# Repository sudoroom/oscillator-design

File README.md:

#sudosynth
##making music from garbage electronics

KiCad Design for an Oscillator Board
originally by rayendumeldust
contributions by jerkey

license:  GPL V3

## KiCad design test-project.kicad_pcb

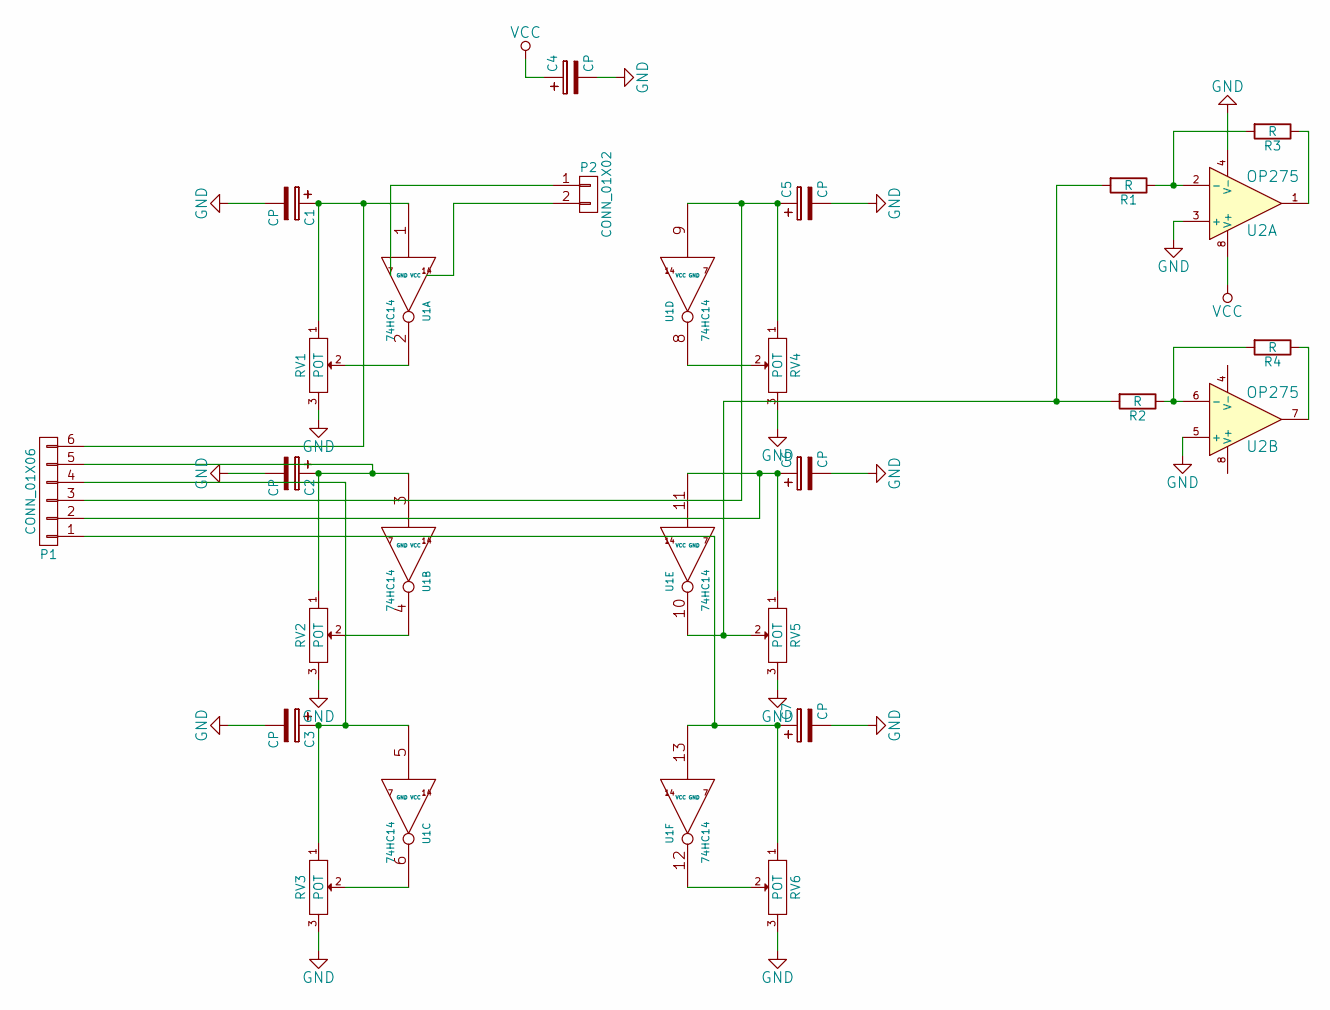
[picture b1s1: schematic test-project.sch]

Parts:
C1, C2, C3, C4, C5: CP; C_Radial_D8_L13_P3.8
C6, C7: CP; C_Radial_D8_L21_P3.8
P1: CONN_01X06; bornier6
P2: CONN_01X02; AK300-2
R1, R2, R3, R4: R; Resistor_Horizontal_RM10mm
RV1, RV2, RV3, RV4, RV5, RV6: POT; Potentiometer_Trimmer-Piher_PT15-B_vertical
U1: 74HC14; DIP-14__300_ELL
U2: OP275; DIP-8__300_ELL

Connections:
GND: C1.2, C2.2, C3.2, C4.2, C5.2, C6.2, C7.2, RV1.3, RV2.3, RV3.3, RV4.3, RV5.3, RV6.3, U2.3 (+), U2.4 (V-), U2.5 (+)
unnamed: C1.1, P1.6, RV1.1, U1.1
unnamed: C2.1, P1.5, RV2.1, U1.3
unnamed: C3.1, P1.4, RV3.1, U1.5
unnamed: C5.1, P1.3, RV4.1, U1.9
unnamed: C6.1, P1.2, RV5.1, U1.11
unnamed: C7.1, P1.1, RV6.1, U1.13
unnamed: P2.1, U1.7 (GND)
unnamed: P2.2, U1.14 (VCC)
unnamed: R1.1, R3.2, U2.2 (-)
unnamed: R1.2, R2.2, RV5.2, U1.10
unnamed: R2.1, R4.2, U2.6 (-)
unnamed: R3.1, U2.1
unnamed: R4.1, U2.7
unnamed: RV1.2, U1.2
unnamed: RV2.2, U1.4
unnamed: RV3.2, U1.6
unnamed: RV4.2, U1.8
unnamed: RV6.2, U1.12
VCC: C4.1, U2.8 (V+)

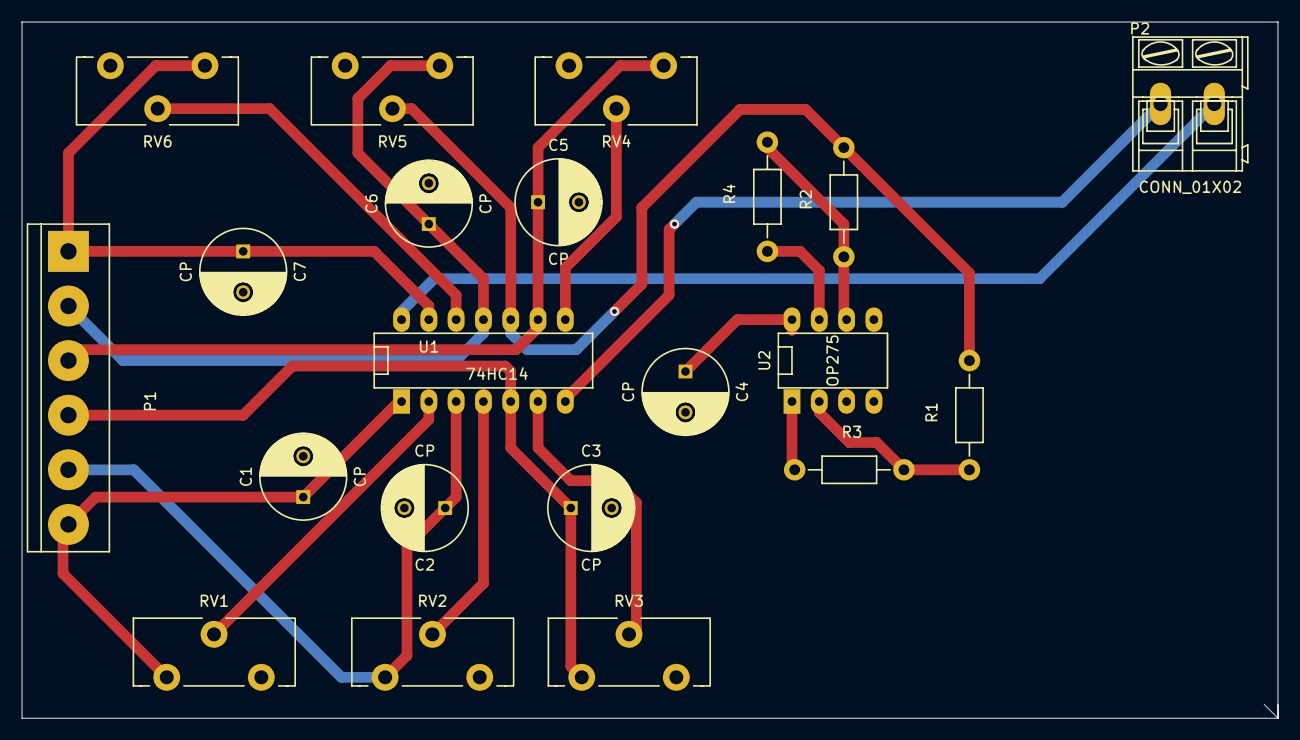
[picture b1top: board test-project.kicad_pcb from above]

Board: 2 copper layers, 116.8 x 64.8 mm, 21 parts (0 on the bottom side), 20 nets.

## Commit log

2015-03-25 first try for the pcb counter is missing some files need to be deleted from the repo
2015-03-25 updated some of the connections
2015-03-25 deleted backup file
2015-03-25 more small changes, forgot to save the project, counter is still missing
2015-03-25 restructuring of the schematic, counter added, EEPROM added
2015-04-01 fixed some missed connections on schematic
2015-04-23 Revert changes made assuming incorrect kicad libraries
    This reverts commit 3a16a8136e794e249657d61b4e54a01cd5eb9d61.
2015-04-24 major details and new parts to EPROM
2015-04-24 change -cache.lib to -default.lib to work with older kicads
    kicad has changed the default schematic library for example resistor
    size, so loading this repo in any but the latest kicad results in
    missed connections on the schematic. putting the contents of -cache.lib
    as the first library in the project ensures that older kicads will get
    the correct parts, for example for resistors.
    http://www.kicad-pcb.org/display/KICAD/Migration+from+old+stable+to+latest
2015-04-24 we should still be tracking -cache.lib
2015-04-24 move things to be closer together on schematic
2015-04-24 add schematic image and update README.md
2015-05-15 remove ground connections to pots
2015-05-25 add a pair of 74LS138 chips
2015-05-25 add header for oscillator inputs, update schematic.png
